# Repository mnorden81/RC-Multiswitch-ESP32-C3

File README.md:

# RC-Multiswitch-ESP32-C3

RC-Multiswitch mit 8 Schaltkanaelen auf einem ESP32-C3 SuperMini.

Frueher `CRSF-Multiswitch-ESP32-C3`. Der neue Name ist neutral, weil der Multiswitch neben CRSF auch SBUS (UART A) als Eingang versteht.

Kleiner, guenstiger Multiswitch fuer RC-Modelle: Der ESP32-C3 empfaengt CRSF vom Empfaenger und schaltet ueber einen TBD62083APG (Nachfolger des ULN2803A) bis zu 8 Verbraucher (Licht, Relais, Funktionen). Das Layout folgt dem CRSF Multiswitch THT v1.1, alle Bauteile ausser den JST-GH-Buchsen sind bedrahtet.

Dokumente:
- [docs/Projektbeschreibung.docx](docs/Projektbeschreibung.docx): Projektbeschreibung
- [docs/Hardware-Beschreibung_C3_S3.docx](docs/Hardware-Beschreibung_C3_S3.docx): Hardware-Beschreibung C3 und S3 (Stecker, Kanalzuordnung, Stueckliste, Dimensionierung)
- [docs/Abnahmepruefung.md](docs/Abnahmepruefung.md): Abnahmepruefung (Pruefliste fuer ein fertig gebautes Modul)
- [docs/Firmware-Spezifikation.md](docs/Firmware-Spezifikation.md) (auch als DOCX): Firmware-Spezifikation (Basis V3, Router fuer Modulketten, BOOT-Taster, Status-LED)

## Merkmale
- 8 Schaltkanaele ueber TBD62083APG (negativ) oder TBD62783APG (positiv), Kontroll-LED je Kanal
- UART A (Eingang vom Empfaenger) und UART B (Rolle waehlbar: Modulkette CRSF, S.Port-LiPo-Sensoren oder GPS)
- Versorgung des ESP32 aus +5 V des Empfaengers, Last getrennt mit 5-12 V
- Eigener THT-Footprint fuer den SuperMini im Projekt

## Hardware (v0.3 (Entwurf))
Board: ESP32-C3 SuperMini

- Lastspannung 5-12 V (VLOAD) an CN2 (JST PH 2), TVS-Diode P6KE18A als Schutz.
- Treiber TBD62083APG (DMOS, Nachfolger des ULN2803A, gleiche Pinbelegung; ein ULN2803A passt weiterhin in den Sockel), 8 Kanaele, max. 500 mA je Kanal, Summe aller Kanaele ca. 1,5 A. Spannungsabfall am Ausgang nur ca. 0,2-0,4 V statt ca. 1 V beim ULN2803A. Positiv schaltende Variante mit TBD62783APG siehe [hardware/README-hardware.md](hardware/README-hardware.md).
- R9-R16 (THT 1/4 W) zwischen Treiber-Ausgang und Stiftleiste J1: kein Wert vorgegeben, der Anwender legt sie passend zu Verbraucher und Lastspannung aus.
- R1-R8 und LED1-LED8 (3 mm) als Kontroll-LED je Kanal, vom Steuersignal Sn gegen GND. Werte legt der Anwender fest, eine Empfehlung ist auf der Platine aufgedruckt.
- Keine Pulldowns und keine Widerstaende in den UART-Leitungen. Der ESP32 wird aus +5 V von CN1 (BEC/Empfaenger) versorgt.

### Belegung
| Funktion | GPIO |
|---|---|
| S0..S7 | IO0..IO7 |
| UART A (CN1, Eingang) | RX IO20, TX IO21 |
| UART B (J5) | TX IO10, RX IO8 |

### Anschluesse
- CN1 UART A (JST-GH 4): 1 GND, 2 +5 V, 3 RX, 4 TX
- J5 UART B (JST-GH 4): 1 GND, 2 +5 V, 3 TX, 4 RX (1:1-Kabel zum naechsten Modul)
- CN2 Last 5-12 V (JST PH 2, max. ca. 2 A je Kontakt)
- J1 Ausgaenge S0..S7

### Hinweise
- IO8 haengt beim SuperMini an der Onboard-LED, IO9 am BOOT-Taster. UART B RX liegt auf IO8.
- **Risiko IO2 (Ausgang 3):** IO2 ist ein Strapping-Pin und muss beim Einschalten HIGH sein. LED3/R3 und der Treiber-Eingang koennen ihn nach LOW ziehen, der C3 startet dann evtl. nicht sicher. Die Platine bleibt so (bereits bestellt). Beim ersten Aufbau mehrmals ein- und ausschalten; Abhilfe siehe [firmware/README.md](firmware/README.md#bekanntes-risiko-c3-io2-ausgang-3-ist-ein-strapping-pin).
- Footprint ESP32-C3-SuperMini_THT ist eine eigene Zeichnung (2x8, 2,54 mm, Reihenabstand 15,24 mm). Vor der Fertigung 1:1 am echten Board pruefen.

## Firmware (v4.08)
- Arduino-Sketch `firmware/RC_Multiswitch`, gleicher Quellcode fuer C3 und S3 (Board wird automatisch erkannt). Basis: MultiSwitch_ESP32_V3 v3.12.
- CRSF auf UART A (Werkseinstellung ab v4.07), wahlweise SBUS. UART B (und UART C beim S3) per Lua oder Web-UI auf Aus, CRSF (Modulkette), S.Port, GPS oder Raw einstellbar, mit eigener Baudrate je UART. Beim GPS sucht die Baudrate „Auto“ (Vorgabe) die Rate selbst und stellt das GPS auf 115200 Baud und 10 Hz um, wie bei Betaflight. In der Modulkette ist jedes Modul mit eigener Adresse ueber Lua einzeln einstellbar.
- Gemeinsame Basis aller ESP32-Module seit v4.05: `firmware/RC_Multiswitch/src/RC_Common/` (CRSF-Bibliothek mit Router, UART-Rollen, Lua-Menue, NVS, WLAN-Failsafe, Status-LED, OTA), siehe deren README.
- BOOT-Taster 3 s: WLAN-AP ein/aus. Status-LED nur beim S3.
- Details und Bauanleitung: [firmware/README.md](firmware/README.md).

## Firmware flashen

Es gibt drei Wege. Ein neues Modul wird einmal per USB geflasht (Weg 1 oder Weg 2), danach geht jedes Update bequem per WLAN (Weg 3).

| Weg | Braucht | Einstellungen im Modul |
|---|---|---|
| 1. Fertige Datei aus GitHub + Web-Flasher | nur Chrome oder Edge | werden **gelöscht** |
| 2. Arduino IDE | Arduino IDE 2.x | bleiben erhalten |
| 3. Update per WLAN | Handy oder PC mit WLAN | bleiben erhalten |

Der Sketch ist für C3 und S3 derselbe, das Board wird automatisch erkannt. Für dieses Repo (ESP32-C3 SuperMini) gilt das Artefakt `RC_Multiswitch-C3` und die Einstellungen unten.

### Weg 1: Fertige Firmware aus GitHub (ohne Arduino IDE)

GitHub baut die Firmware bei jeder Änderung automatisch (Workflow „Firmware bauen“).

1. Auf GitHub angemeldet sein (sonst gibt es keinen Download-Knopf).
2. In diesem Repo oben auf **Actions** klicken, links den Workflow **Firmware bauen** wählen.
3. Den obersten Lauf mit grünem Haken öffnen (Branch `main`).
4. Ganz unten unter **Artifacts** **RC_Multiswitch-C3** herunterladen und die ZIP-Datei entpacken. Darin liegen u. a. `RC_Multiswitch.ino.merged.bin` (Komplett-Image für USB) und `RC_Multiswitch.ino.bin` (nur für Weg 3).
   Steht dort nichts (Artefakte werden nach 90 Tagen gelöscht): rechts oben **Run workflow** → **Run workflow** klicken, nach ca. 3 Minuten ist ein neuer Lauf fertig.
5. ESP32-C3 SuperMini mit einem USB-C-**Datenkabel** an den PC stecken (kein reines Ladekabel). Ein Treiber ist unter Windows 10/11 nicht nötig.
6. In **Chrome** oder **Edge** die Seite https://espressif.github.io/esptool-js/ öffnen (Espressif-Web-Flasher, Firefox geht nicht).
7. **Connect** klicken und den COM-Port des Moduls wählen. Klappt das nicht: Baudrate oben auf `115200` stellen und das Modul mit der BOOT-Taste in den Flash-Modus bringen (siehe Weg 2, „Wenn das Hochladen nicht klappt“).
8. Unter **Flash Address** `0x0` eintragen, mit **Datei auswählen** die `.merged.bin` wählen, dann **Program** klicken.
9. Wenn unten „Leaving…“ steht, das USB-Kabel kurz abziehen und wieder einstecken. Fertig.

> **Achtung:** Das Komplett-Image überschreibt den ganzen Flash (4 MB). Alle Einstellungen und die Sicherungen im Flash sind danach weg. Vorher in der Weboberfläche die Einstellungen als Datei sichern (Karte **Konfiguration sichern/wiederherstellen** → „Als Datei exportieren“) und hinterher dort wieder importieren. Wer die Einstellungen behalten will, nimmt Weg 2 oder 3.

### Weg 2: Arduino IDE

**Einmalig einrichten**

1. Arduino IDE 2.x installieren (https://www.arduino.cc/en/software).
2. **Datei → Einstellungen → Zusätzliche Boardverwalter-URLs**: `https://espressif.github.io/arduino-esp32/package_esp32_index.json` eintragen.
3. **Werkzeuge → Board → Boardverwalter**: „esp32“ suchen, **esp32 von Espressif Systems** in Version **3.0.7** installieren.
4. **Werkzeuge → Bibliotheken verwalten**: **Bolder Flight Systems SBUS 8.1.4**, **TinyGPSPlus 1.0.3** suchen und in genau dieser Version installieren.
   Alles andere (z. B. `src/RC_Common/`) liegt schon im Sketch-Ordner.

**Flashen**

1. Repo herunterladen: oben auf GitHub **Code → Download ZIP**, entpacken (oder den vorhandenen Ordner nehmen).
2. In der Arduino IDE **Datei → Öffnen** und `firmware/RC_Multiswitch/RC_Multiswitch.ino` wählen.
3. Unter **Werkzeuge** einstellen:

   | Einstellung | Wert |
   |---|---|
   | Board | **ESP32C3 Dev Module** |
   | USB CDC On Boot | **Enabled** (Pflicht, sonst Abbruch mit Meldung) |
   | Flash Size | 4MB (32Mb) |
   | Partition Scheme | **Default 4MB with spiffs (1.2MB APP/1.5MB SPIFFS)** |
   | Erase All Flash Before Sketch Upload | **Disabled** (sonst sind die Einstellungen weg) |

4. ESP32-C3 SuperMini mit einem USB-C-**Datenkabel** an den PC stecken (kein reines Ladekabel). Ein Treiber ist unter Windows 10/11 nicht nötig. Dann unter **Werkzeuge → Port** den neuen COM-Port wählen.
5. Auf den Pfeil **Hochladen** klicken. Am Ende steht „Hard resetting via RTS pin…“.
6. Das Modul startet von selbst neu. Wenn nicht: USB-Kabel kurz abziehen und wieder einstecken.

**Wenn das Hochladen nicht klappt** („Failed to connect“ oder „No serial data received“): USB abziehen, die Taste **BOOT** gedrückt halten, USB wieder einstecken, BOOT loslassen. Das Modul ist jetzt im Flash-Modus. Unter **Werkzeuge → Port** ggf. den neuen COM-Port wählen und noch einmal **Hochladen**. Danach das USB-Kabel einmal abziehen und wieder einstecken.

### Weg 3: Update per WLAN (OTA)

1. Die Datei `RC_Multiswitch.ino.bin` besorgen: aus GitHub (Weg 1, Schritte 1–4) oder in der Arduino IDE mit **Sketch → Kompilierte Binärdatei exportieren** (liegt dann im Sketch-Ordner unter `build/`). Nicht die `.merged.bin` nehmen.
2. WLAN des Moduls einschalten: BOOT-Taste 3 s halten (oder Lua „WLAN“ bzw. automatisch nach 60 s ohne RC-Signal). Name **MultiSwitch**, Passwort `123456789` (falls nicht geändert).
3. Mit Handy oder PC in dieses WLAN gehen und im Browser http://192.168.1.1 öffnen.
4. Reiter **WiFi**, Karte **Firmware-Update (OTA)**: die `.bin`-Datei auswählen und hochladen. Das Modul startet danach neu, die Einstellungen bleiben erhalten.

Schlägt das Update fehl, läuft die alte Firmware einfach weiter. Das Modul beim Update am besten über den Empfänger/BEC versorgen, nicht nur über einen schwachen USB-Anschluss.

## Ordner
- `hardware/`: KiCad-Projekt (Schaltplan, PCB, PDF, eigene Footprints, fp-lib-table). Entwurfsnotizen in [hardware/README-hardware.md](hardware/README-hardware.md). 3D-druckbares Gehaeuse (stehende oder gewinkelte Stiftleiste) in [hardware/gehaeuse/](hardware/gehaeuse/README.md).
- `firmware/`: Firmware v4.08 (Arduino-Sketch).
- `docs/`: Projektbeschreibung, Hardware-Beschreibung und Firmware-Spezifikation.

## Stand
- Hardware: Schaltplan und PCB vorhanden. ERC/DRC noch in KiCad ausfuehren.
- Firmware: v4.08 kompiliert fuer C3 und S3, noch nicht auf Hardware getestet.

## Offene Punkte
- Pad-Namen und Footprint am realen Board pruefen
- Erwaermung des Treibers bei mehreren Kanaelen mit 500 mA pruefen
- Firmware auf Hardware testen (Einzelmodul und Kette mit 2-3 Modulen)
- IO2-Strapping (Ausgang 3) beim ersten Aufbau pruefen

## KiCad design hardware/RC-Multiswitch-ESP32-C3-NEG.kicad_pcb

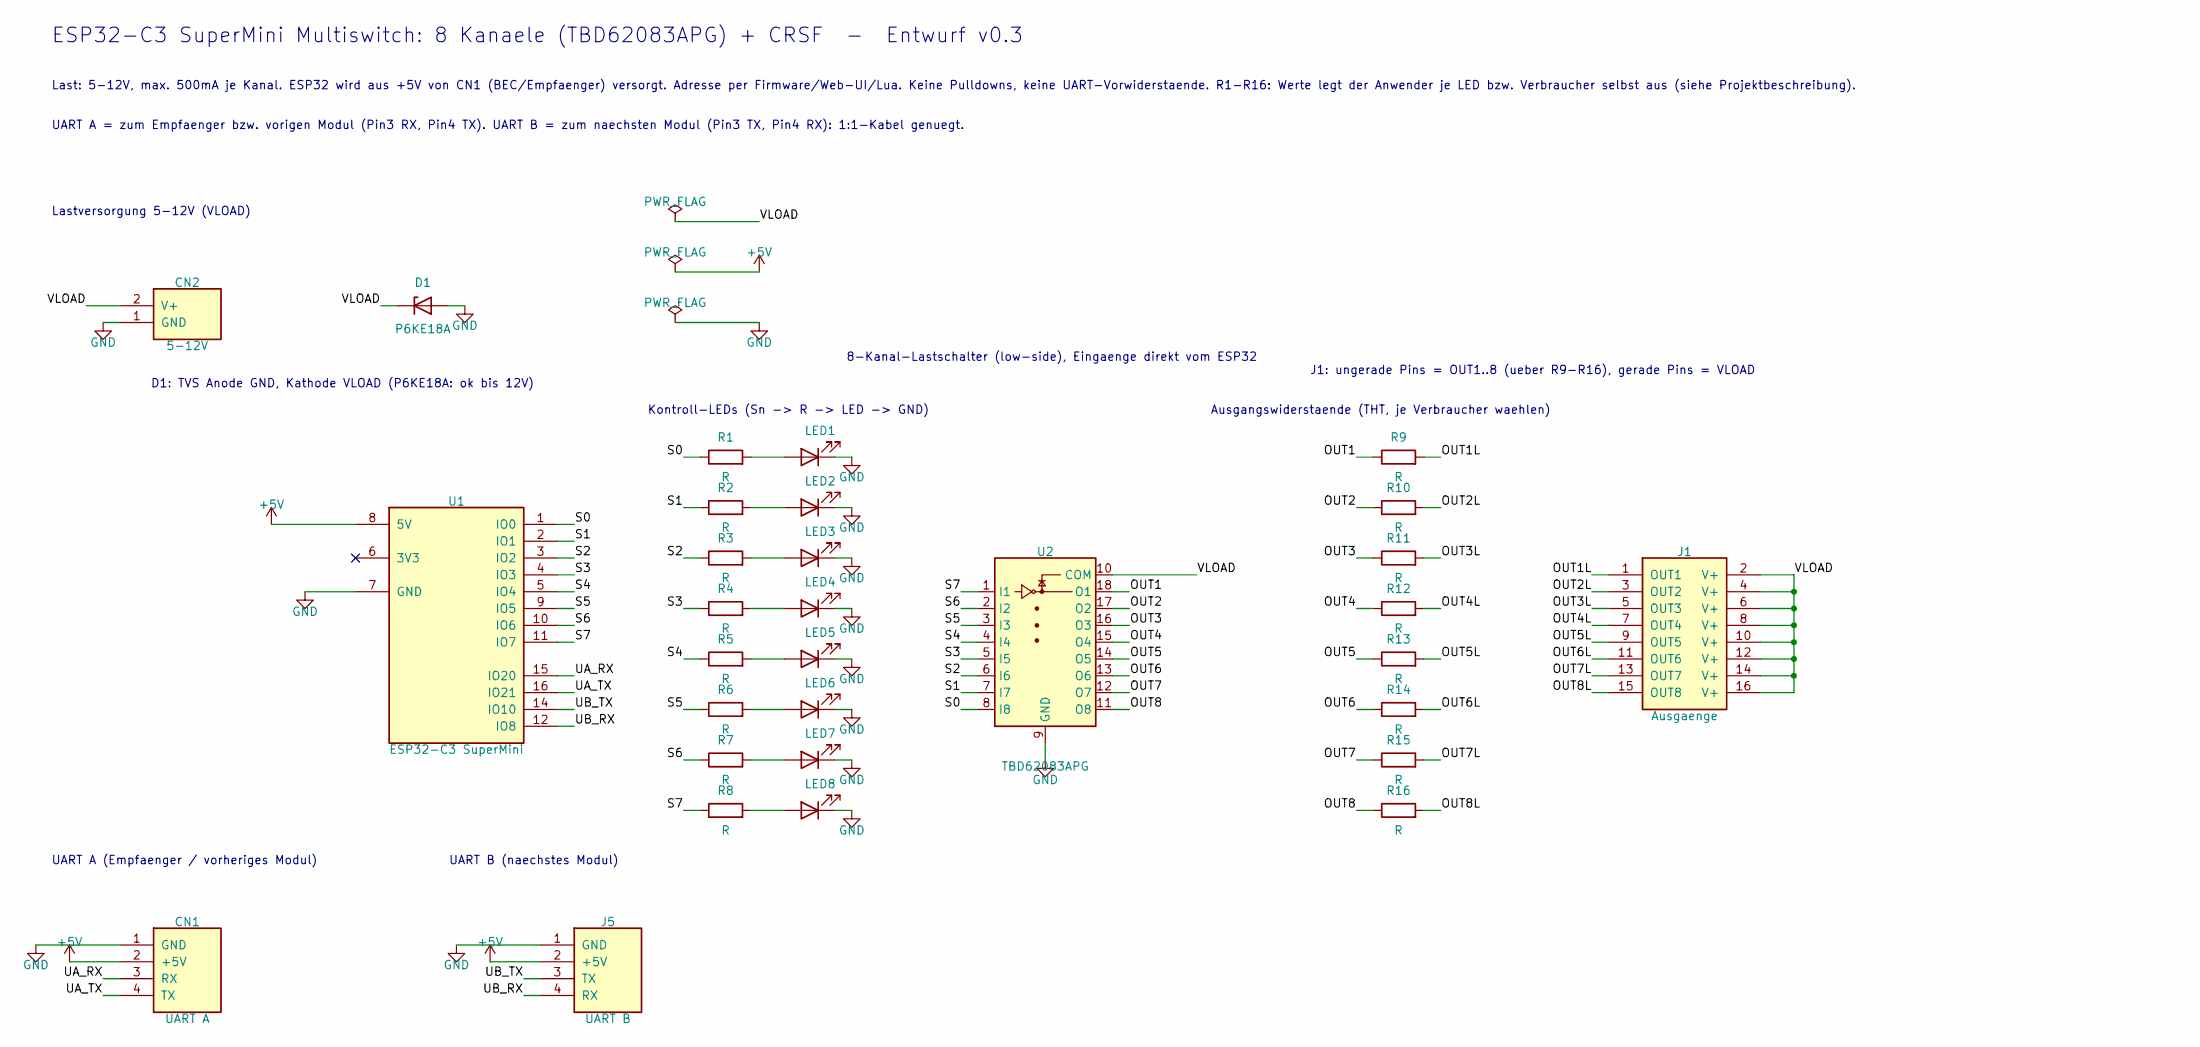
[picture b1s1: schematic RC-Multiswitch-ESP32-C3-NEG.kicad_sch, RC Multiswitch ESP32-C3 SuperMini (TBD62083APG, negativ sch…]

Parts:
CN1: UART A; JST_PH_S4B-PH-K_1x04_P2.00mm_Horizontal
CN2: 5-12V; JST_PH_S2B-PH-K_1x02_P2.00mm_Horizontal
D1: P6KE18A; D_DO-15_P12.70mm_Horizontal
J1: Ausgaenge; PinHeader_2x08_P2.54mm_Vertical
J5: UART B; JST_PH_S4B-PH-K_1x04_P2.00mm_Horizontal
LED1, LED2, LED3, LED4, LED5, LED6, LED7, LED8: LED; LED_D3.0mm
R1, R2, R3, R4, R5, R6, R7, R8, R9, R10, R11, R12, R13, R14, R15, R16: R; R_Axial_DIN0207_L6.3mm_D2.5mm_P7.62mm_Horizontal
U1: ESP32-C3 SuperMini; ESP32-C3-SuperMini_THT
U2: TBD62083APG; DIP-18_W7.62mm_Socket

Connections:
+5V: CN1.2 (+5V), J5.2 (+5V), U1.8 (5V)
/OUT1: R9.1, U2.18 (O1)
/OUT1L: J1.1 (OUT1), R9.2
/OUT2: R10.1, U2.17 (O2)
/OUT2L: J1.3 (OUT2), R10.2
/OUT3: R11.1, U2.16 (O3)
/OUT3L: J1.5 (OUT3), R11.2
/OUT4: R12.1, U2.15 (O4)
/OUT4L: J1.7 (OUT4), R12.2
/OUT5: R13.1, U2.14 (O5)
/OUT5L: J1.9 (OUT5), R13.2
/OUT6: R14.1, U2.13 (O6)
/OUT6L: J1.11 (OUT6), R14.2
/OUT7: R15.1, U2.12 (O7)
/OUT7L: J1.13 (OUT7), R15.2
/OUT8: R16.1, U2.11 (O8)
/OUT8L: J1.15 (OUT8), R16.2
/S0: R1.1, U1.1 (IO0), U2.8 (I8)
/S1: R2.1, U1.2 (IO1), U2.7 (I7)
/S2: R3.1, U1.3 (IO2), U2.6 (I6)
/S3: R4.1, U1.4 (IO3), U2.5 (I5)
/S4: R5.1, U1.5 (IO4), U2.4 (I4)
/S5: R6.1, U1.9 (IO5), U2.3 (I3)
/S6: R7.1, U1.10 (IO6), U2.2 (I2)
/S7: R8.1, U1.11 (IO7), U2.1 (I1)
/UA_RX: CN1.3 (RX), U1.15 (IO20)
/UA_TX: CN1.4 (TX), U1.16 (IO21)
/UB_RX: J5.4 (RX), U1.12 (IO8)
/UB_TX: J5.3 (TX), U1.14 (IO10)
/VLOAD: CN2.2 (V+), D1.1 (K), J1.2 (V+), J1.4 (V+), J1.6 (V+), J1.8 (V+), J1.10 (V+), J1.12 (V+), J1.14 (V+), J1.16 (V+), U2.10 (COM)
GND: CN1.1 (GND), CN2.1 (GND), D1.2 (A), J5.1 (GND), LED1.1 (K), LED2.1 (K), LED3.1 (K), LED4.1 (K), LED5.1 (K), LED6.1 (K), LED7.1 (K), LED8.1 (K), U1.7 (GND), U2.9 (GND)
unnamed: LED1.2 (A), R1.2
unnamed: LED2.2 (A), R2.2
unnamed: LED3.2 (A), R3.2
unnamed: LED4.2 (A), R4.2
unnamed: LED5.2 (A), R5.2
unnamed: LED6.2 (A), R6.2
unnamed: LED7.2 (A), R7.2
unnamed: LED8.2 (A), R8.2

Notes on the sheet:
Ausgangswiderstaende (THT, je Verbraucher waehlen)
J1: ungerade Pins = OUT1..8 (ueber R9-R16), gerade Pins = VLOAD
Last: 5-12V, max. 500mA je Kanal. ESP32 wird aus +5V von CN1 (BEC/Empfaenger) versorgt. Adresse per Firmware/Web-UI/Lua. Keine Pulldowns, keine UART-Vorwiderstaende. R1-R16: Werte legt der Anwender je LED bzw. Verbraucher selbst aus (siehe Projektbeschreibung).
D1: TVS Anode GND, Kathode VLOAD (P6KE18A: ok bis 12V)
8-Kanal-Lastschalter (low-side), Eingaenge direkt vom ESP32
UART A = zum Empfaenger bzw. vorigen Modul (Pin3 RX, Pin4 TX). UART B = zum naechsten Modul (Pin3 TX, Pin4 RX): 1:1-Kabel genuegt.
UART A (Empfaenger / vorheriges Modul)
Kontroll-LEDs (Sn -> R -> LED -> GND)
Lastversorgung 5-12V (VLOAD)
UART B (naechstes Modul)
ESP32-C3 SuperMini Multiswitch: 8 Kanaele (TBD62083APG) + CRSF - Entwurf v0.3

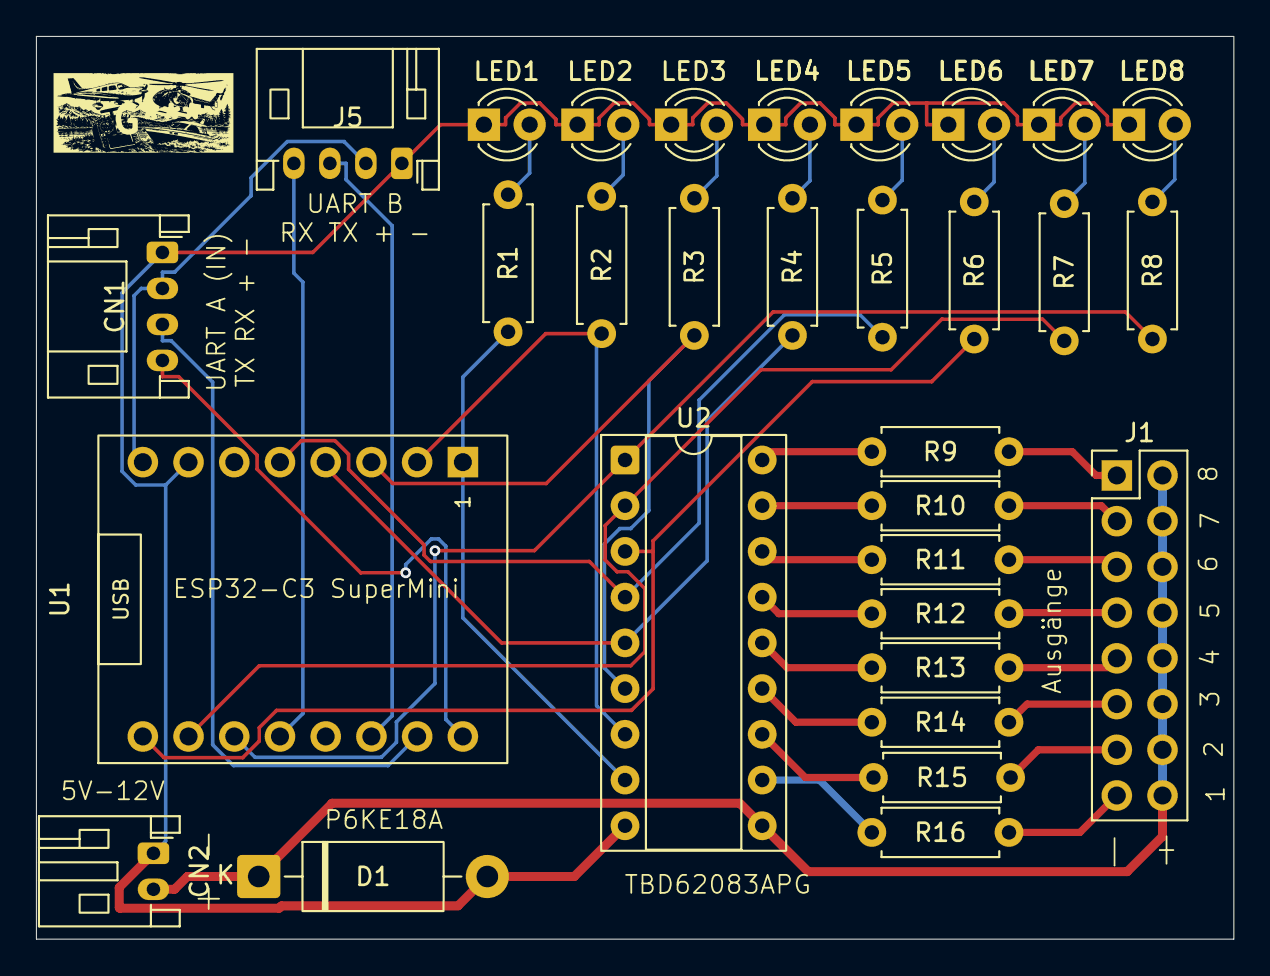
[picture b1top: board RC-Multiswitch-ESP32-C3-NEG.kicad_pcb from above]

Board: 2 copper layers, 66.5 x 50.2 mm, 31 parts (0 on the bottom side), 39 nets.
